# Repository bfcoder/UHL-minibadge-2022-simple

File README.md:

# UHL-minibadge-2022-simple
Utah Home Labs Simple Minibadge for 2022

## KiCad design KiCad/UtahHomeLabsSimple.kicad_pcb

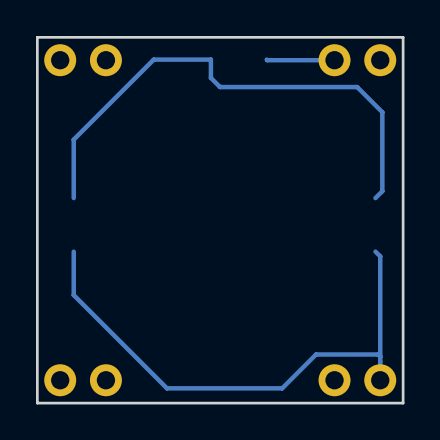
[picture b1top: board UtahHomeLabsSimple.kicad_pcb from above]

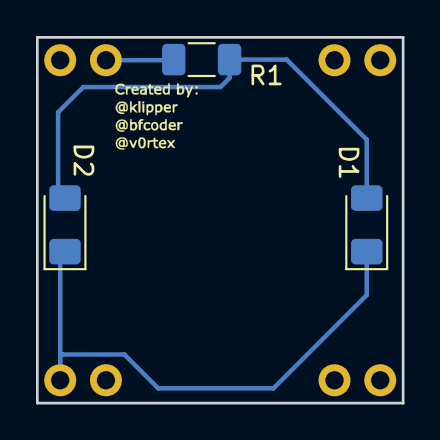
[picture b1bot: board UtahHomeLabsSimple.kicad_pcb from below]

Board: 2 copper layers, 20.3 x 20.3 mm, 5 parts (3 on the bottom side), 3 nets.

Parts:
D1, D2: LED; LED_1206_3216Metric_Pad1.42x1.75mm_HandSolder
R1: R_US; R_1206_3216Metric_Pad1.30x1.75mm_HandSolder
Ref**: Val**; UHLSimple_Svg
X1: SAINTCON-Minibadge-Simple

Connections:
unnamed: D1.1 (K), D2.1 (K), X1.16 (GND)
unnamed: D1.2 (A), D2.2 (A), R1.2
unnamed: R1.1, X1.7 (+3v3)

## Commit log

2022-07-08 Added Original Files
    Original Files
2022-07-08 Updates
    Updated Schema to Parallel
2022-07-08 Re-did traces
    Traces re-done
2022-07-08 Moved Trace labels
2022-07-08 Fixed silkscreens / cutouts
2022-07-17 Updated Graphics
2022-07-17 Adjust labels and trace segments
    Move labels into better positions.
    Adjust a few of the traces.
